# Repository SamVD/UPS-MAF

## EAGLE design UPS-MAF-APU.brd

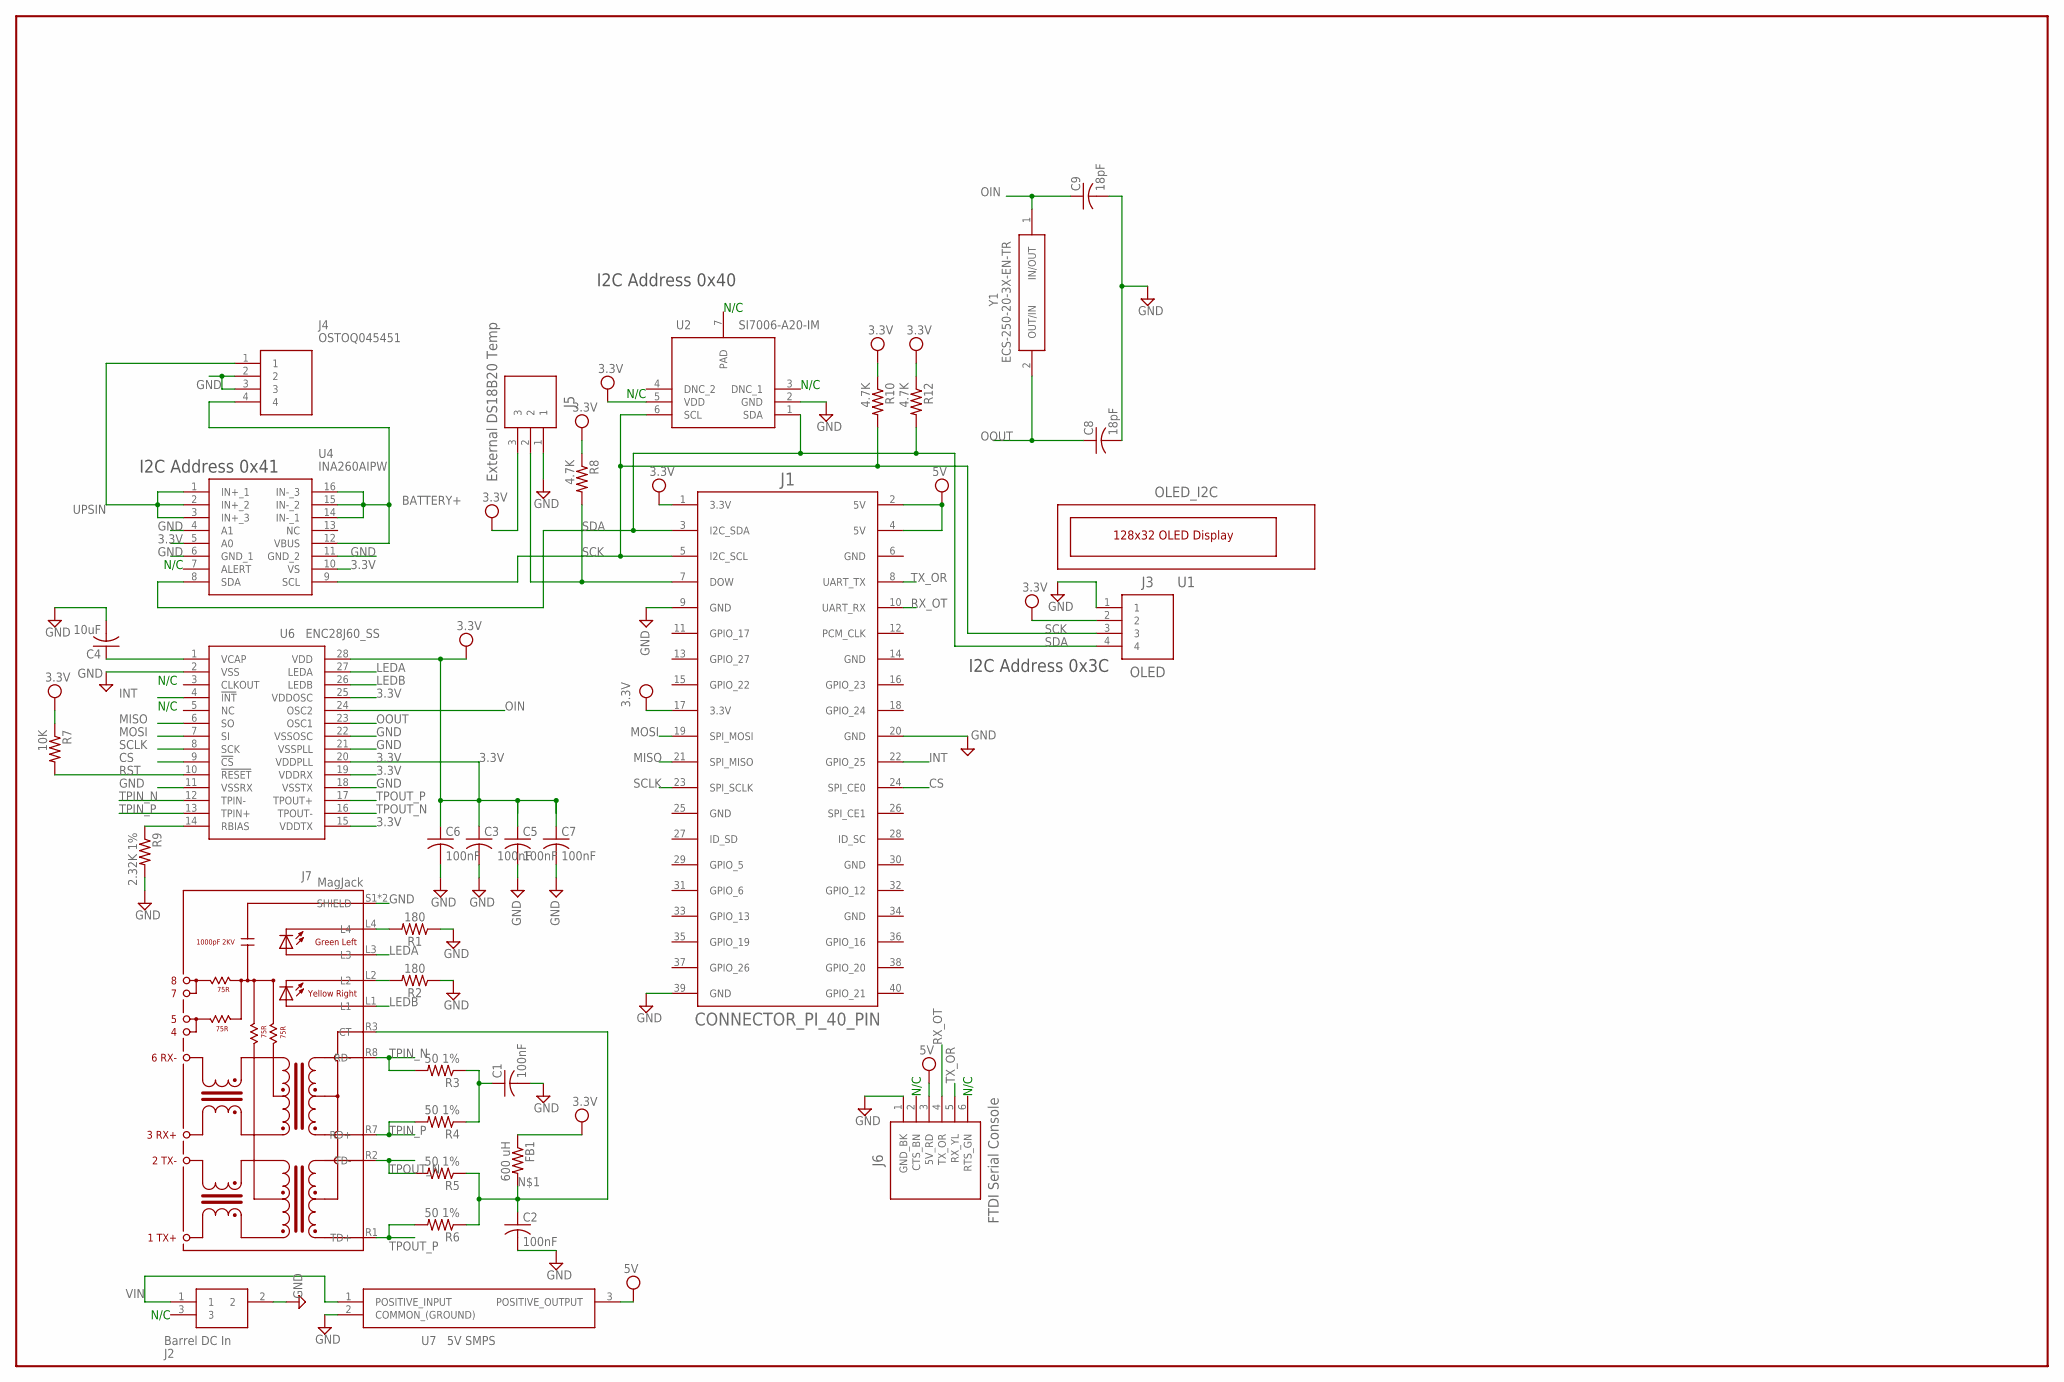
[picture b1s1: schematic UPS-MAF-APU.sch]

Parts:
C1, C2, C3, C5, C6, C7: 100nF; C0603
C4: 10uF; C0805
C8, C9: 18pF; C0603
FB1: 600 uH; R0805
J1: CONNECTOR_PI_40_PIN; 2X20
J2: Barrel DC In; PJ-102AH
J3: OLED; ESQ-104-XX-X-S
J4: OSTOQ045451
J5: External DS18B20 Temp; MOLEX_70553-0002
J6: FTDI Serial Console; ESQ-106-XX-X-S
J7: MagJack; WIZNET_RB1-125BAG1A
R1, R2: 180; 0603
R3, R4, R5, R6: 50 1%; R0805
R7: 10K; R0805
R8, R10, R12: 4.7K; R0805
R9: 2.32K 1%; R0805
U1: OLED_I2C; OLED-I2C
U2: SI7006-A20-IM; SON100P300X300X80-7N
U4: INA260AIPW; SOP65P640X120-16N
U6: ENC28J60_SS; SOP65P780X200-28N
U7: 5V SMPS; OKI-78SR-HORIZONTAL
Y1: ECS-250-20-3X-EN-TR; ECS250203XENTR

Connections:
3.3V: C3.1, C5.1, C6.1, C7.1, FB1.1, J1.1 (3.3V), J1.17 (3.3V), J3.2, J5.3, R7.1, R8.1, R10.1, R12.1, U2.5 (VDD), U4.5 (A0), U4.10 (VS), U6.15 (VDDTX), U6.19 (VDDRX), U6.20 (VDDPLL), U6.25 (VDDOSC), U6.28 (VDD)
5V: J1.2 (5V), J1.4 (5V), J6.3 (5V_RD), U7.3 (POSITIVE_OUTPUT)
BATTERY+: J4.4, U4.12 (VBUS), U4.14 (IN-_1), U4.15 (IN-_2), U4.16 (IN-_3)
CS: J1.24 (SPI_CE0), U6.9 (!CS)
GND: C1.2, C2.2, C3.2, C4.2, C5.2, C6.2, C7.2, C8.2, C9.2, J1.9 (GND), J1.20 (GND), J1.39 (GND), J2.2, J3.1, J4.2, J4.3, J5.1, J6.1 (GND_BK), J7.S1 (SHIELD), J7.S2 (SHIELD), R1.1, R2.1, R9.2, U2.2 (GND), U4.4 (A1), U4.6 (GND_1), U4.11 (GND_2), U6.2 (VSS), U6.11 (VSSRX), U6.18 (VSSTX), U6.21 (VSSPLL), U6.22 (VSSOSC), U7.2 (COMMON_(GROUND))
INT: J1.22 (GPIO_25), U6.4 (!INT)
LEDA: J7.L3, U6.27 (LEDA)
LEDB: J7.L1, U6.26 (LEDB)
MISO: J1.21 (SPI_MISO), U6.6 (SO)
MOSI: J1.19 (SPI_MOSI), U6.7 (SI)
unnamed: C2.1, FB1.2, J7.R3 (CT), R5.1, R6.1
unnamed: C4.1, U6.1 (VCAP)
unnamed: J1.7 (DOW), J5.2, R8.2
unnamed: J7.L2, R2.2
unnamed: C1.1, R3.1, R4.1
unnamed: J7.L4, R1.2
unnamed: R9.1, U6.14 (RBIAS)
OIN: C9.1, U6.24 (OSC2), Y1.1 (IN/OUT)
OOUT: C8.1, U6.23 (OSC1), Y1.2 (OUT/IN)
PAD: U2.7 (PAD)
RST: R7.2, U6.10 (!RESET)
RX_OT: J1.10 (UART_RX), J6.4 (TX_OR)
SCK: J1.5 (I2C_SCL), J3.3, R10.2, U2.6 (SCL), U4.9 (SCL)
SCLK: J1.23 (SPI_SCLK), U6.8 (SCK)
SDA: J1.3 (I2C_SDA), J3.4, R12.2, U2.1 (SDA), U4.8 (SDA)
TPIN_N: J7.R8 (RD-), R3.2, U6.12 (TPIN-)
TPIN_P: J7.R7 (RD+), R4.2, U6.13 (TPIN+)
TPOUT_N: J7.R2 (TD-), R5.2, U6.16 (TPOUT-)
TPOUT_P: J7.R1 (TD+), R6.2, U6.17 (TPOUT+)
TX_OR: J1.8 (UART_TX), J6.5 (RX_YL)
UPSIN: J4.1, U4.1 (IN+_1), U4.2 (IN+_2), U4.3 (IN+_3)
VIN: J2.1, U7.1 (POSITIVE_INPUT)

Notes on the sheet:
I2C Address 0x3C
I2C Address 0x40
I2C Address 0x41
N/C

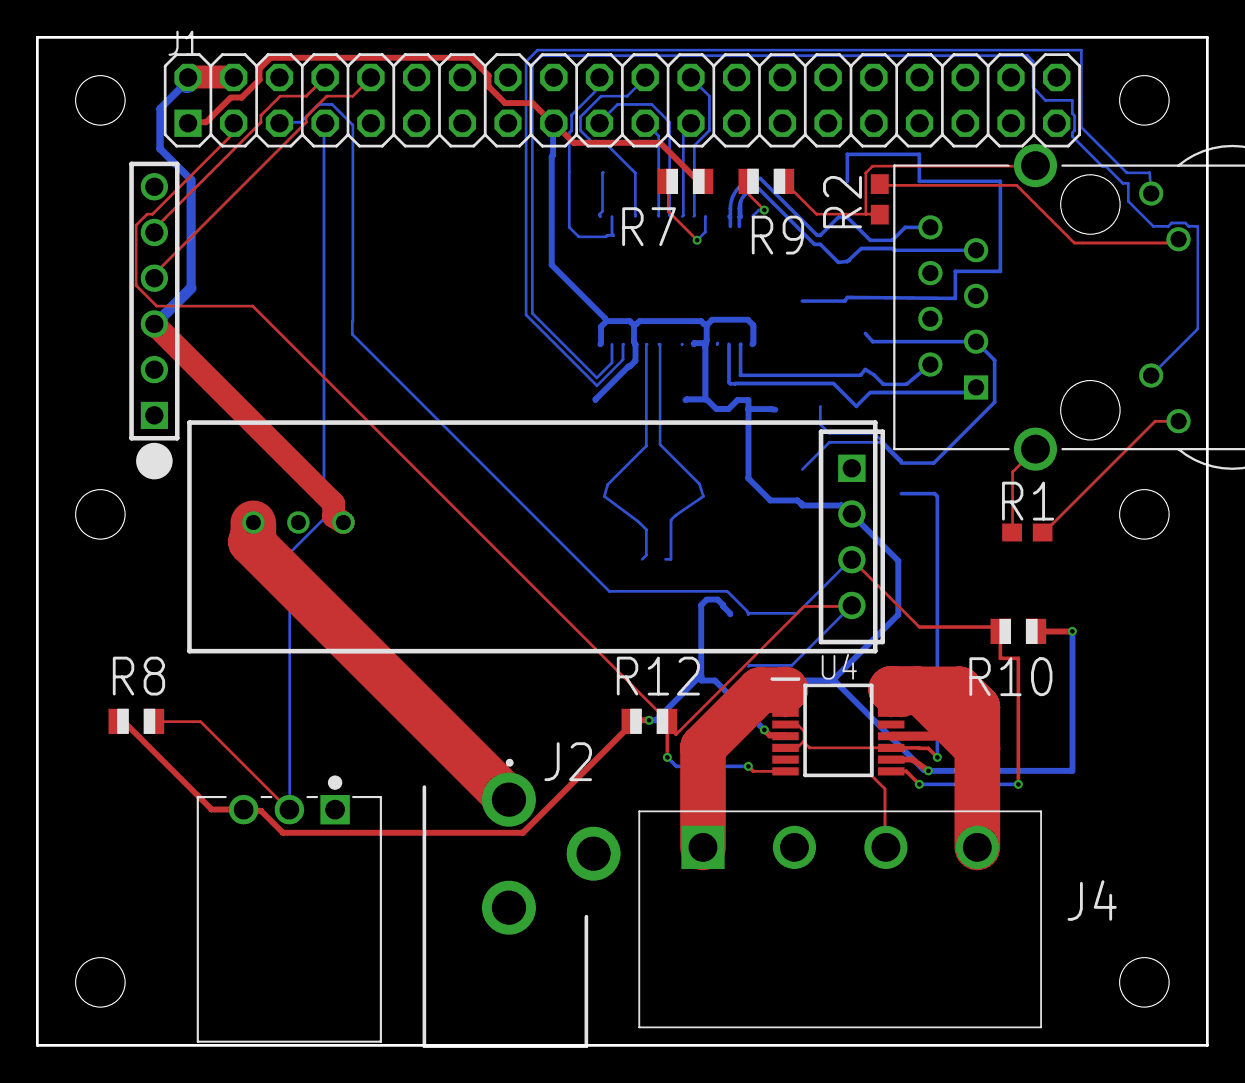
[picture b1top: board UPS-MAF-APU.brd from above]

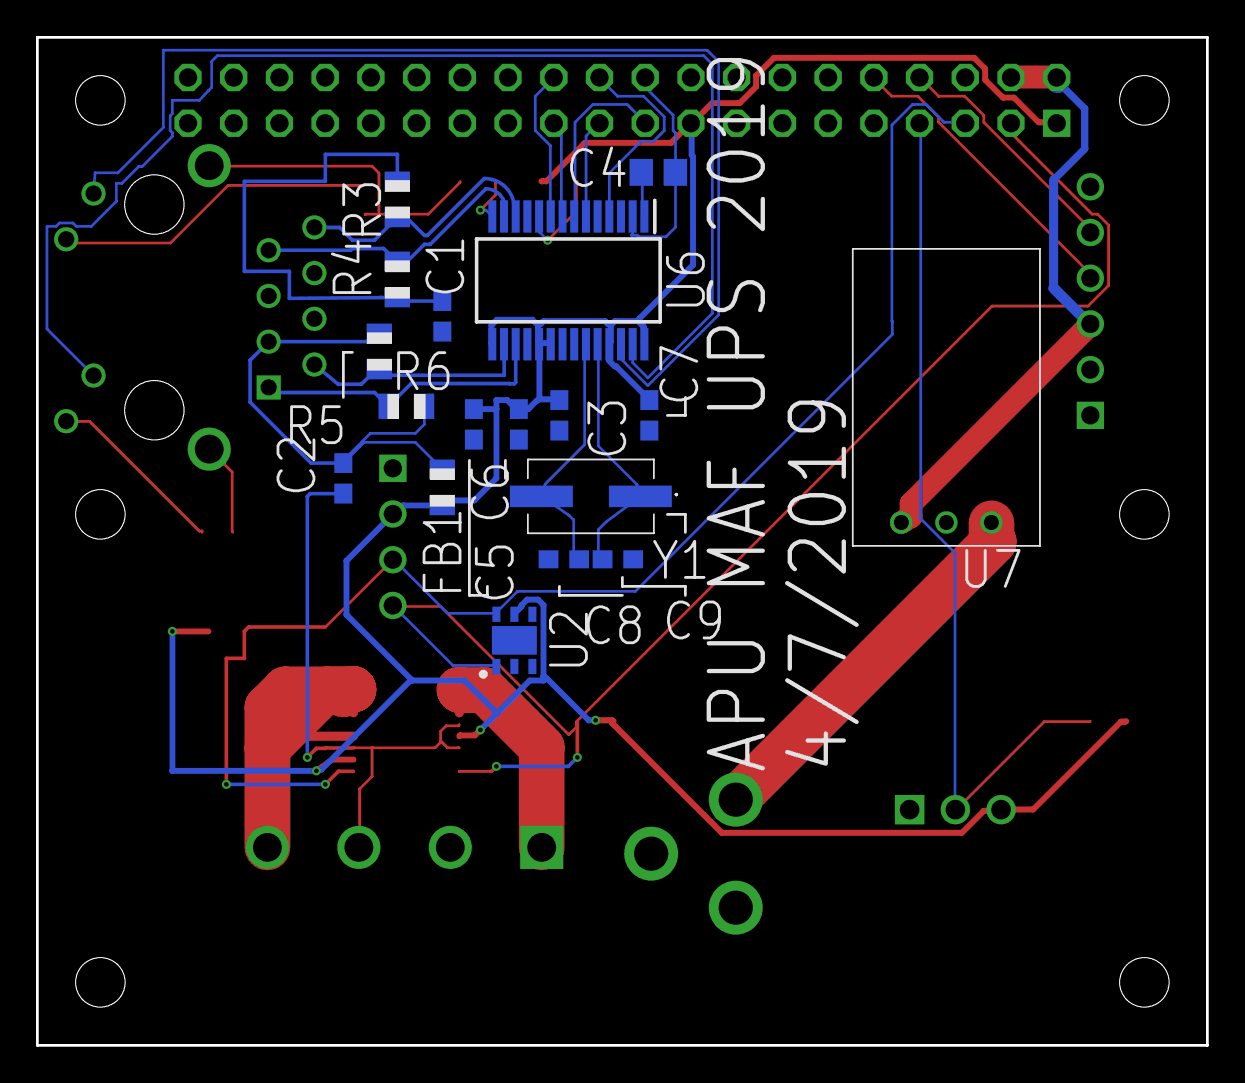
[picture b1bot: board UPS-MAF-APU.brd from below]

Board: 2 copper layers, 65.0 x 56.0 mm, 34 parts (18 on the bottom side), 31 nets.

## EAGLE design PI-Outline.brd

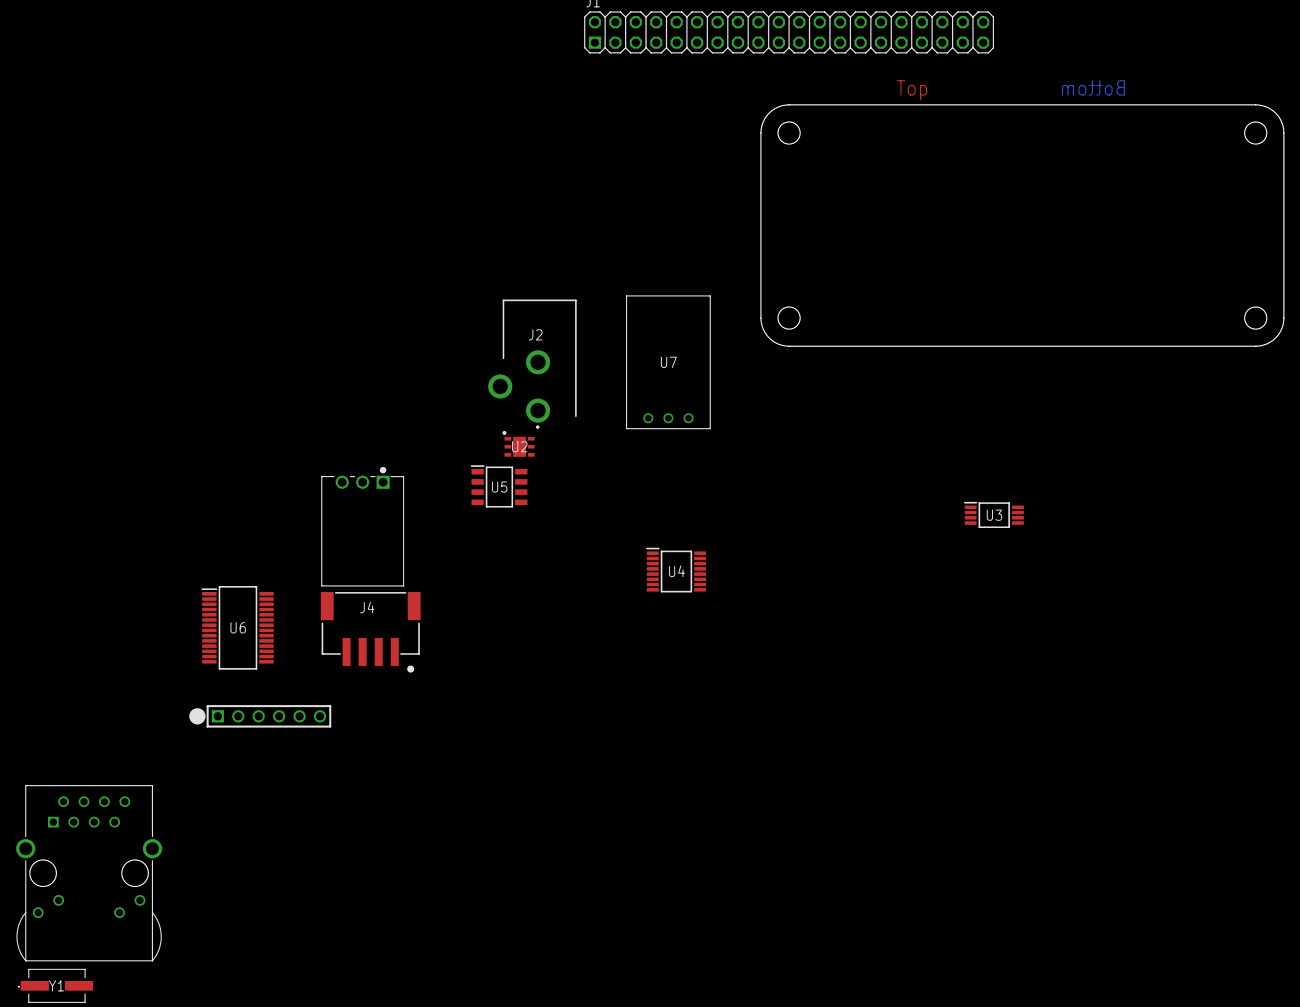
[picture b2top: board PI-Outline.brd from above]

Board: 2 copper layers, 65.0 x 30.0 mm, 13 parts (0 on the bottom side), 9 nets, no tracks yet.

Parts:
J1: CONNECTOR_PI_40_PIN; 2X20
J2: Barrel DC In; PJ-102AH
J4: VE.Direct Serial; S4B-PH-SM4-TB
J5: External DS18B20 Temp; MOLEX_70553-0002
J6: FTDI Serial Console; ESQ-106-XX-X-S
J7: MagJack; WIZNET_RB1-125BAG1A
U2: SI7006-A20-IM; SON100P300X300X80-7N
U3: HAT EEPROM; SOP65P640X120-8N
U4: INA260AIPW; SOP65P640X120-16N
U5: Isolator; SOIC127P600X175-8N
U6: ENC28J60_SS; SOP65P780X200-28N
U7: 5V SMPS; OKI-78SR-HORIZONTAL
Y1: ECS-250-20-3X-EN-TR; ECS250203XENTR

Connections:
3.3V: J5.3, J6.3, U4.5, U4.10, U6.19, U6.20, U6.25, U6.28
BATTERY+: U4.12, U4.14, U4.15, U4.16
BATTERY-: U4.1, U4.2, U4.3
unnamed: J7.R2, U6.16
unnamed: J7.R1, U6.17
S$1: J5.1, J6.1, J7.S1, J7.S2, U2.2, U6.2, U6.18, U6.21, U6.22
S$2: U4.4, U4.6, U4.11
S$3: U2.1, U4.8
S$5: U2.6, U4.9

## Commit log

2019-03-26 README
2019-03-28 deleted and re-created .brd file to get them back in sync.
    Please enter the commit message for your changes. Lines starting

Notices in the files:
parts and their libraries:
SparkFun-Resistors: Licensing: Creative Commons ShareAlike 4.0 International - https://creativecommons.org/licenses/by-sa/4.0
